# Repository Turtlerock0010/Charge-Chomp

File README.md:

# Charge-Chomp

> An image of the hardware 3D model

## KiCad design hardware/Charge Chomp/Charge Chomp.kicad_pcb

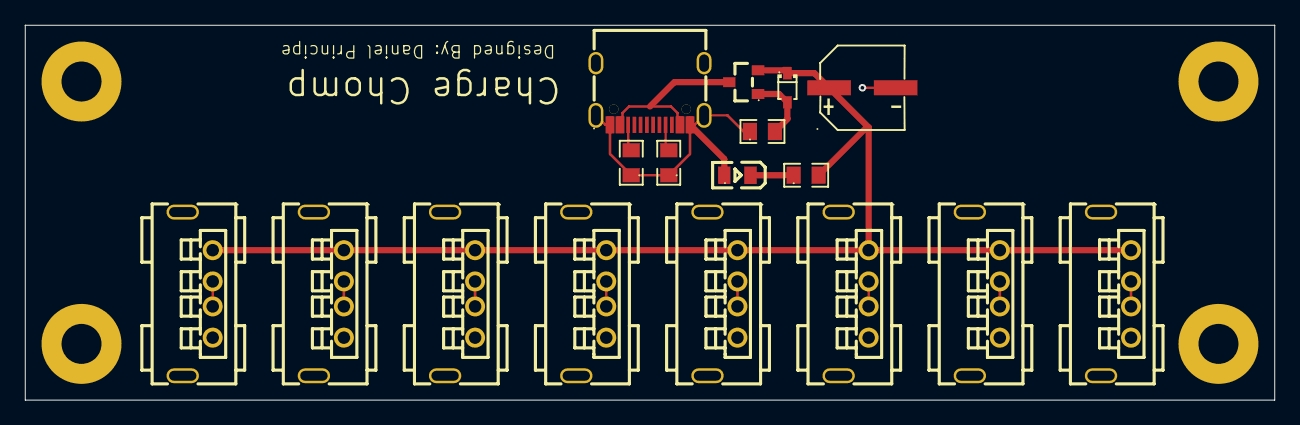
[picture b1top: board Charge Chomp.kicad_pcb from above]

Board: 2 copper layers, 100.0 x 30.0 mm, 17 parts (0 on the bottom side), 15 nets.

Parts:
C1: 220µF; C4747974_CAP-SMD_BD6_3-L6_6-W6_6-LS7_2-FD
D1: LED; C84260_LED0805-R-RD
D2: Z5V6; C22612_SOD-323_L1_8-W1_3-LS2_5-RD
J2, J3, J4, J5, J6, J7, J8, J9: USB_A; C456015_USB-A-TH_AF-ZJB13_7
Q1: AO3401A; C15127_SOT-23_L2_9-W1_3-P1_90-LS2_4-BR
R1, R2: 5.1K; C27834_R0805
R3: 330Ω; C17630_R0805
R4: 10K; C2907219_R0805
USBC1: TYPE-C-31-M-12; C165948_USB-C_SMD-TYPE-C-31-M-12_1

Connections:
+5V: Q1.3 (D), USBC1.A4B9 (VBUS), USBC1.B4A9 (VBUS)
GND: C1.2, D1.1 (K), J2.4 (GND), J3.4 (GND), J4.4 (GND), J5.4 (GND), J6.4 (GND), J7.4 (GND), J8.4 (GND), J9.4 (GND), R1.1, R2.1, R4.1, USBC1.1 (EH), USBC1.2 (EH), USBC1.3 (EH), USBC1.4 (EH), USBC1.A1B12 (GND), USBC1.B1A12 (GND)
unnamed: D1.2 (A), R3.1
unnamed: J2.2 (D-), J2.3 (D+)
unnamed: J3.2 (D-), J3.3 (D+)
unnamed: J4.2 (D-), J4.3 (D+)
unnamed: J5.2 (D-), J5.3 (D+)
unnamed: J6.2 (D-), J6.3 (D+)
unnamed: J7.2 (D-), J7.3 (D+)
unnamed: J8.2 (D-), J8.3 (D+)
unnamed: J9.2 (D-), J9.3 (D+)
unnamed: D2.2, Q1.1 (G), R4.2
unnamed: R1.2, USBC1.A5 (CC1)
unnamed: R2.2, USBC1.B5 (CC2)
VCC: C1.1, D2.1, J2.1 (VBUS), J3.1 (VBUS), J4.1 (VBUS), J5.1 (VBUS), J6.1 (VBUS), J7.1 (VBUS), J8.1 (VBUS), J9.1 (VBUS), Q1.2 (S), R3.2
